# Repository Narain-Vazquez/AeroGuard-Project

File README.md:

# UIC Senior Design Project 

### PCB Design Contributors:

Narain Vazquez  
Nico Gomez

### Repository Description:

This repository specifically holds the contents of the electrical portion of the Aeroguard Project, including the schematics for our PCB design, power distribution, and system integration.  

All included files are designed to work specifically with **KiCad**, and the project files created for this project can be found in the following directories:  

- `libraries_v4` – contains custom KiCad libraries created for the project.  
- `rpi-aeroguard-template_v4` – contains the KiCad project files and PCB templates for the Aeroguard design.

### Aeroguard Description & Demo:

The Aeroguard Project is a senior design initiative focused on developing an autonomous aerial monitoring system. The system runs on a Linux-based platform and leverages YOLOv11 for real-time detection of fires, smoke, and safety equipment protocol. Video is streamed over RTMP, and the system can trigger alerts using speakers and lights to notify personnel of hazards or protocol violations.

The video demo showcases our Aeroguard prototype board in action. It demonstrates the fire detection feature, which triggers the speaker alerting system (note: the video itself has no audio).

### Raspberry Pi Compute Module 4 (CM4) Carrier Template

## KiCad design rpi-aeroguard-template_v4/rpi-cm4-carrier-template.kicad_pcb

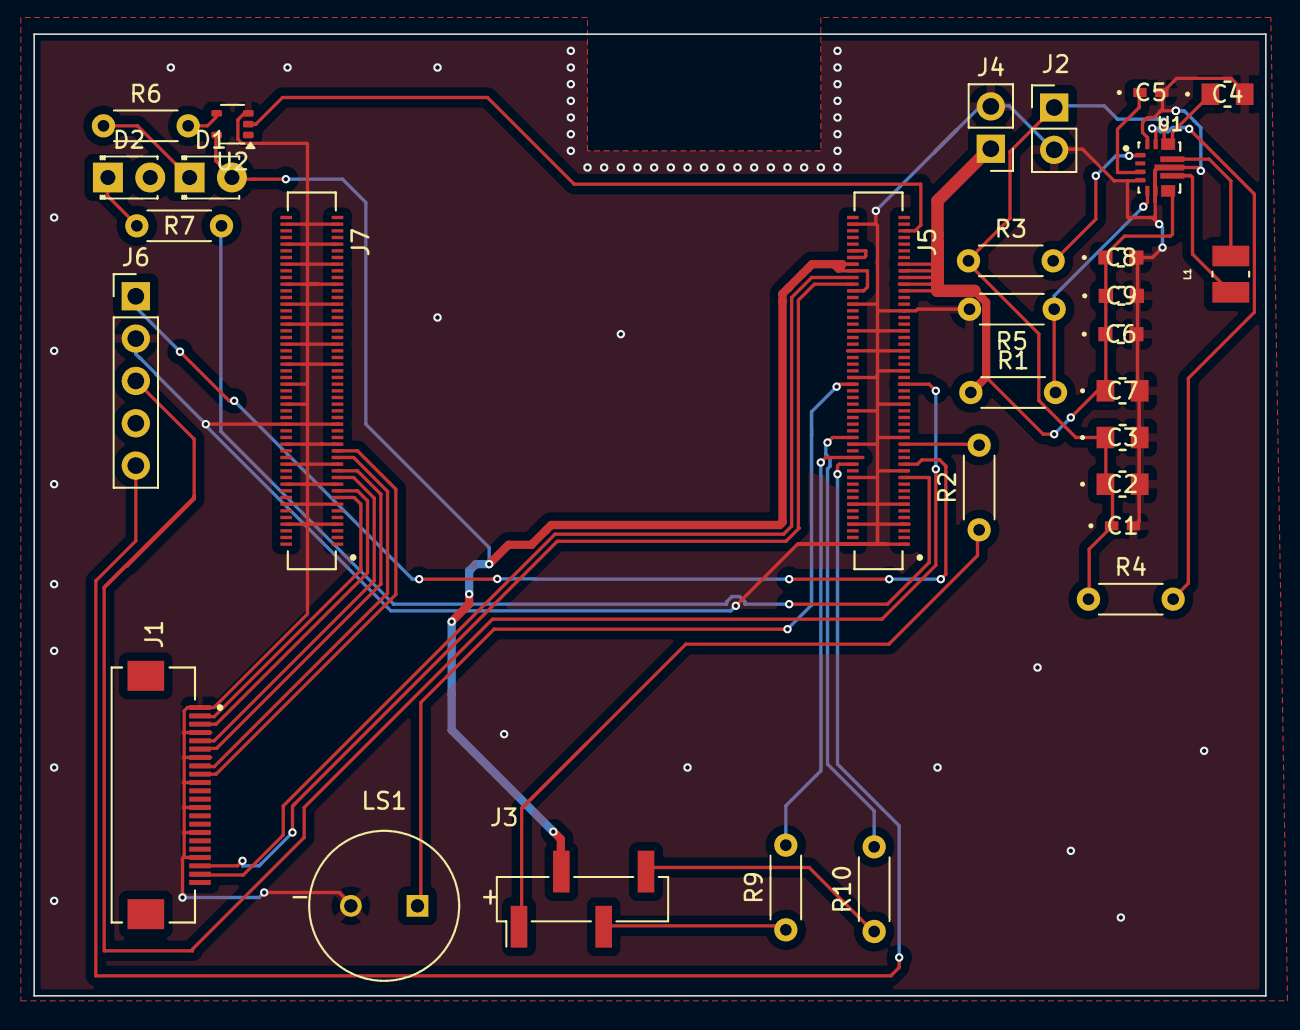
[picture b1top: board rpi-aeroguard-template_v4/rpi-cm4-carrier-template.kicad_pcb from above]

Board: 2 copper layers, 73.9 x 57.7 mm, 31 parts (0 on the bottom side), 34 nets.

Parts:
C1, C5: 0.1uF; CAP_CL05_SAM-M
C2, C3, C4, C7: 10uF; G-21_MUR-M
C6, C8, C9: 22uF; CAP_CL10_SAM-M
D1: LED Red; LED_D1.8mm_W3.3mm_H2.4mm
D2: LED Green; LED_D1.8mm_W3.3mm_H2.4mm
J1: F305-1A7H1-21022-E100; AMPHENOL_F305-1A7H1-21022-E100
J2, J4: Conn_01x02_Pin; PinHeader_1x02_P2.54mm_Vertical
J3: Conn_01x04_Pin; PinHeader_1x04_P2.54mm_Vertical_SMD_Pin1Left
J5, J7: DF40C-100DS-0.4V_51_; HIROSE_DF40C-100DS-0.4V_51_
J6: Conn_01x05_Pin; PinHeader_1x05_P2.54mm_Vertical
L1: 1.5uH; INDC2520X100N
LS1: CST-931AP; CUI_CST-931AP
R1: 365k; R_Axial_DIN0204_L3.6mm_D1.6mm_P5.08mm_Horizontal
R2, R9, R10: 220; R_Axial_DIN0204_L3.6mm_D1.6mm_P5.08mm_Horizontal
R3, R4: 10k; R_Axial_DIN0204_L3.6mm_D1.6mm_P5.08mm_Horizontal
R5: 68.1k; R_Axial_DIN0204_L3.6mm_D1.6mm_P5.08mm_Horizontal
R6, R7: 1k; R_Axial_DIN0204_L3.6mm_D1.6mm_P5.08mm_Horizontal
U1: TPS63070RNMR; VREG_TPS63070RNMR
U2: 74LVC1G07SE-7; SOT-353_SC-70-5

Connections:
+1.8V: J5.88, J5.90
+3.3V: D1.2 (A), J3.2, J5.78, J5.84, J5.86, U2.5 (VCC)
+5V: C6.1, C7.1, C8.1, C9.1, J4.1, J5.77, J5.79, J5.81, J5.83, J5.85, R1.1, U1.7_8 (VOUT)
/CM4 GPIO/GPIO17: J5.50, LS1.P
/CM4 GPIO/GPIO18: J5.49, J6.3
/CM4 GPIO/GPIO19: J5.26, J6.5
/CM4 GPIO/GPIO21: J5.25, J6.1
/CM4 GPIO/GPIO 5: J5.34, R10.2
/CM4 GPIO/GPIO 12: J5.31, R2.2
/CM4 GPIO/GPIO 13: J5.28, R9.2
/CM4 GPIO/PI_nLED_Activity: J5.21, R7.2
/CM4 GPIO/nPWR_LED: J5.95, U2.2
/CM4 High Speed/CAM0_C_N: J1.8, J7.27
/CM4 High Speed/CAM0_C_P: J1.9, J7.29
/CM4 High Speed/CAM0_D0_N: J1.2, J7.15
/CM4 High Speed/CAM0_D0_P: J1.3, J7.17
/CM4 High Speed/CAM0_D1_N: J1.5, J7.21
/CM4 High Speed/CAM0_D1_P: J1.6, J7.23
/CM4 High Speed/SCL1: J1.20, J5.80
/CM4 High Speed/SDA1: J1.21, J5.82
EN: R4.2, U1.14 (EN)
FB: R1.2, R5.1, U1.5 (FB)
GND: C1.2, C2.2, C3.2, C4.2, C5.2, C6.2, C7.2, C8.2, C9.2, J1.1, J1.4, J1.7, J1.10, J1.13, J1.16, J1.19, J2.2, J4.2, J5.1, J5.2, J5.7, J5.8, J5.13, J5.14, J5.22, J5.23, J5.32, J5.33, J5.42, J5.43, J5.52, J5.53, J5.59, J5.60, J5.65, J5.66, J5.71, J5.74, J5.98, J6.2, J7.7, J7.8, J7.13, J7.14, J7.19, J7.20, J7.25, J7.26, J7.31, J7.32, J7.37, J7.38, J7.44, J7.50, J7.55, J7.56, J7.61, J7.62, J7.67, J7.68, J7.73, J7.74, J7.79, J7.80, J7.85, J7.86, J7.91, J7.92, J7.97, J7.98, LS1.M, R5.2, U1.4 (GND), U1.6 (FB2), U1.10 (PGND), U1.15 (VSEL), U2.3 (GND)
unnamed: D1.1 (K), R6.1
unnamed: D2.1 (K), R7.1
unnamed: J3.1, R2.1
unnamed: J3.3, R9.1
unnamed: J3.4, R10.1
unnamed: R6.2, U2.4
unnamed: L1.1, U1.11 (L1)
unnamed: L1.2, U1.9 (L2)
unnamed: C5.1, U1.3 (VAUX)
PS: R3.2, U1.1 (PS/SYNC)
VIN: C1.1, C2.1, C3.1, C4.1, J2.1, R3.1, R4.1, U1.12_13 (VIN)

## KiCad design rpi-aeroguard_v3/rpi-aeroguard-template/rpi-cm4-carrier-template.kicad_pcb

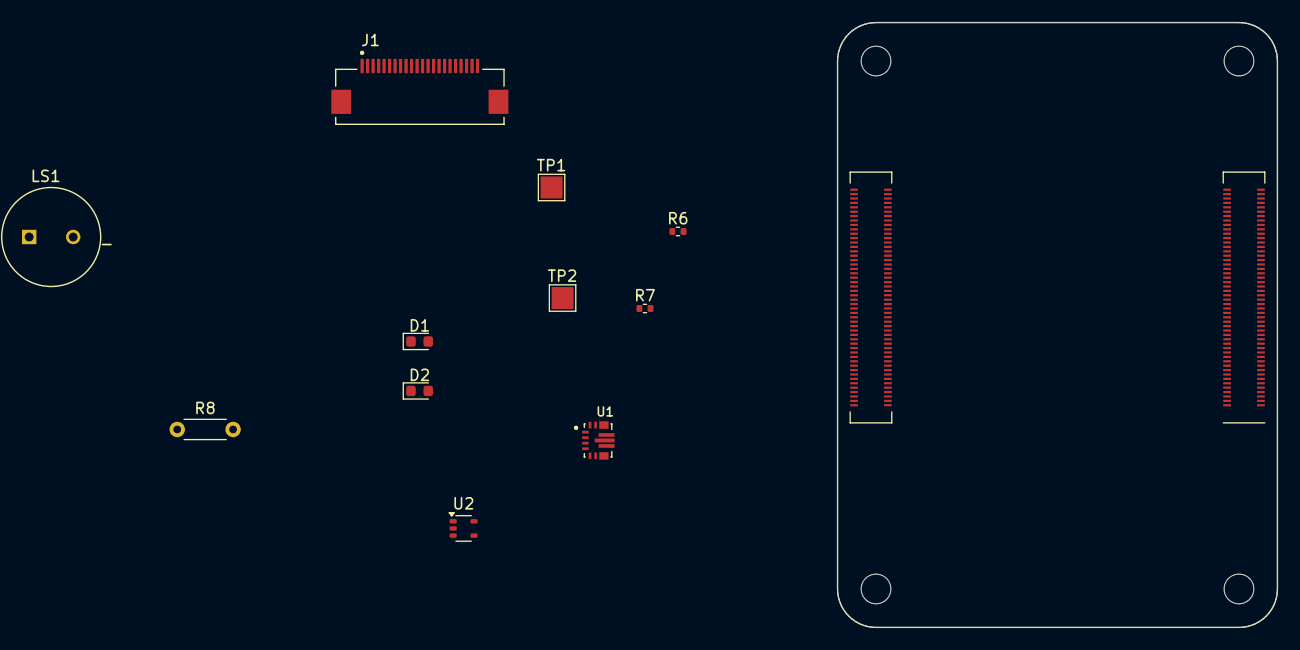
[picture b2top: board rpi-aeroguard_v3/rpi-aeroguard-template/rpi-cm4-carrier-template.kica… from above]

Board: 2 copper layers, 40.0 x 55.0 mm, 12 parts (0 on the bottom side), 19 nets, no tracks yet.

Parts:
D1: LED Red; LED_0603_1608Metric
D2: LED Green; LED_0603_1608Metric
J1: F305-1A7H1-21022-E100; AMPHENOL_F305-1A7H1-21022-E100
LS1: CST-931AP; CUI_CST-931AP
Module1: ComputeModule4-CM4; Raspberry-Pi-4-Compute-Module
R6, R7: 1k; R_0402_1005Metric
R8: DNF; R_Axial_DIN0204_L3.6mm_D1.6mm_P5.08mm_Horizontal
TP1, TP2: TestPoint; TestPoint_Pad_2.0x2.0mm
U1: TPS63070RNMR; VREG_TPS63070RNMR
U2: 74LVC1G07SE-7; SOT-353_SC-70-5

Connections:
+1.8V: Module1.88 (+1.8v_(Output)), Module1.90 (+1.8v_(Output))
+3.3V: D1.2 (A), Module1.78 (GPIO_VREF(1.8v/3.3v_Input)), Module1.84 (+3.3v_(Output)), Module1.86 (+3.3v_(Output)), U2.5 (VCC)
+5V: Module1.77 (+5v_(Input)), Module1.79 (+5v_(Input)), Module1.81 (+5v_(Input)), Module1.83 (+5v_(Input)), Module1.85 (+5v_(Input)), Module1.87 (+5v_(Input)), U1.7_8 (VOUT)
/CM4 GPIO/GPIO17: LS1.P, Module1.50 (GPIO17)
/CM4 GPIO/GPIO20: Module1.27 (GPIO20), R8.1
/CM4 GPIO/PI_nLED_Activity: Module1.21 (PI_nLED_Activity), R7.2
/CM4 GPIO/nPWR_LED: Module1.95 (nPI_LED_PWR), U2.2
/CM4 High Speed/CAM0_C_N: J1.8, Module1.127 (CAM1_C_N)
/CM4 High Speed/CAM0_C_P: J1.9, Module1.129 (CAM1_C_P)
/CM4 High Speed/CAM0_D0_N: J1.2, Module1.115 (CAM1_D0_N)
/CM4 High Speed/CAM0_D0_P: J1.3, Module1.117 (CAM1_D0_P)
/CM4 High Speed/CAM0_D1_N: J1.5, Module1.121 (CAM1_D1_N)
/CM4 High Speed/CAM0_D1_P: J1.6, Module1.123 (CAM1_D1_P)
/CM4 High Speed/SCL1: J1.20, Module1.80 (SCL0)
/CM4 High Speed/SDA1: J1.21, Module1.82 (SDA0)
GND: J1.1, J1.4, J1.7, J1.10, J1.13, J1.16, J1.19, LS1.M, Module1.1 (GND), Module1.2 (GND), Module1.7 (GND), Module1.8 (GND), Module1.13 (GND), Module1.14 (GND), Module1.22 (GND), Module1.23 (GND), Module1.32 (GND), Module1.33 (GND), Module1.42 (GND), Module1.43 (GND), Module1.52 (GND), Module1.53 (GND), Module1.59 (GND), Module1.60 (GND), Module1.65 (GND), Module1.66 (GND), Module1.71 (GND), Module1.74 (GND), Module1.98 (GND), Module1.107 (GND), Module1.108 (GND), Module1.113 (GND), Module1.114 (GND), Module1.119 (GND), Module1.120 (GND), Module1.125 (GND), Module1.126 (GND), Module1.131 (GND), Module1.132 (GND), Module1.137 (GND), Module1.138 (GND), Module1.144 (GND), Module1.150 (GND), Module1.155 (GND), Module1.156 (GND), Module1.161 (GND), Module1.162 (GND), Module1.167 (GND), Module1.168 (GND), Module1.173 (GND), Module1.174 (GND), Module1.179 (GND), Module1.180 (GND), Module1.185 (GND), Module1.186 (GND), Module1.191 (GND), Module1.192 (GND), Module1.197 (GND), Module1.198 (GND), U1.4 (GND), U1.6 (FB2), U1.10 (PGND), U1.15 (VSEL), U2.3 (GND)
unnamed: D1.1 (K), R6.1, TP1.1
unnamed: D2.1 (K), R7.1, TP2.1
unnamed: R6.2, U2.4

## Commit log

2025-02-03 Starter template
    buildon top of this
2025-05-15 Create initial

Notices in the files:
rpi-aeroguard-template_v4/rpi-cm4-carrier-template.kicad_pcb:
creativecommons.org/licenses/by/4.0
License: CC BY 4.0
